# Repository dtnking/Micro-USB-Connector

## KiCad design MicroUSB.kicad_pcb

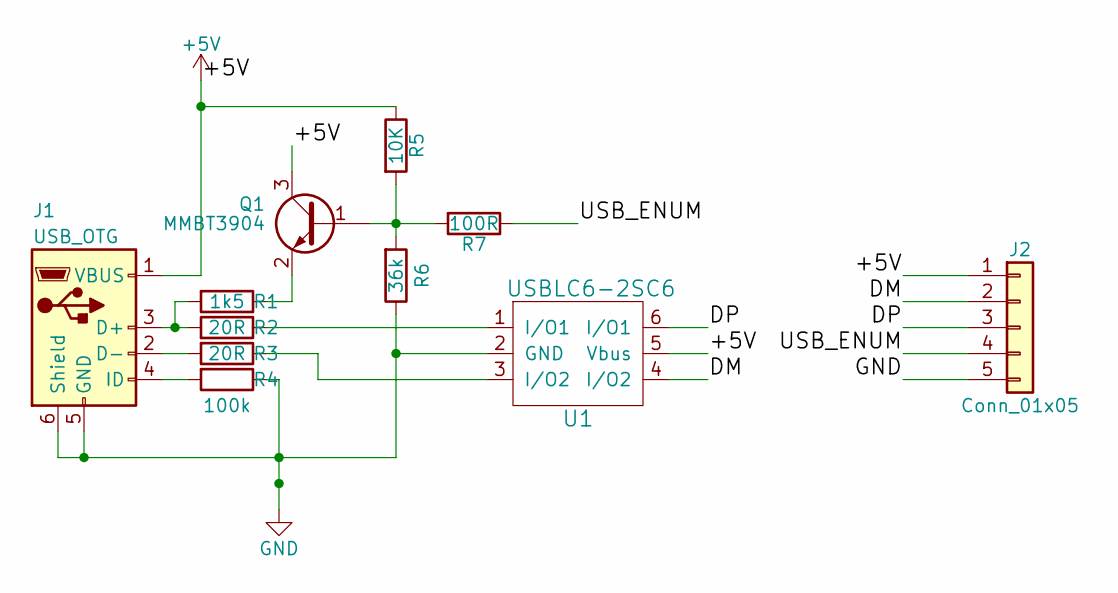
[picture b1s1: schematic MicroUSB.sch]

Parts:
J1: USB_OTG; USB_Micro-B_Molex-105017-0001
J2: Conn_01x05; Pin_Header_Straight_1x05_Pitch2.54mm
Q1: MMBT3904; SOT-23
R1: 1k5; R_0603
R2, R3: 20R; R_0603
R4: 100k; R_0603
R5: 10K; R_0603
R6: 36k; R_0603
R7: 100R; R_0603
U1: USBLC6-2SC6; SOT-23-6

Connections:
+5V: J1.1 (VBUS), J2.1, Q1.3 (C), R5.1, U1.5 (Vbus)
/DM: J2.2, U1.4 (I/O2)
/DP: J2.3, U1.6 (I/O1)
/USB_ENUM: J2.4, R7.1
GND: J1.5 (GND), J1.6 (Shield), J2.5, R4.1, R6.1, U1.2 (GND)
unnamed: J1.2 (D-), R3.2
unnamed: J1.3 (D+), R1.2, R2.2
unnamed: J1.4 (ID), R4.2
unnamed: Q1.1 (B), R5.2, R6.2, R7.2
unnamed: Q1.2 (E), R1.1
unnamed: R2.1, U1.1 (I/O1)
unnamed: R3.1, U1.3 (I/O2)

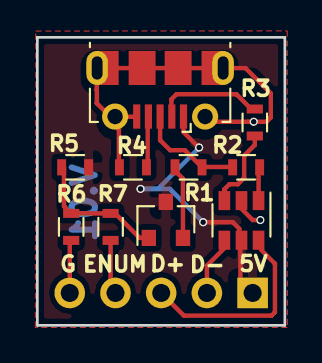
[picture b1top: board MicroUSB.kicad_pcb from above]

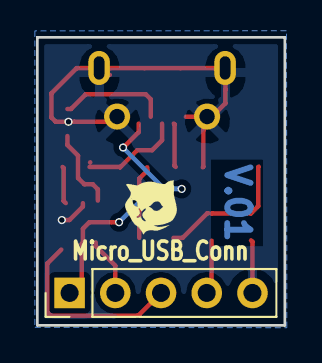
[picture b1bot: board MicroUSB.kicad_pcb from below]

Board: 2 copper layers, 13.8 x 16.0 mm, 12 parts (2 on the bottom side), 12 nets.

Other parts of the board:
Kitty: G***; Kitty

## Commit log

2017-10-12 Added micro usb connector Design
2017-10-13 Re-designed (using non-handsolder footprint)
2017-10-24 Moved the top edge cut further inwards
2017-11-07 Changed the size of text to 0.8x1.0 mm
2017-11-14 Added dimension and changed DM/DP label to D+/D-
2017-11-15 Added a txt V.01 indicated version 1 and added gerber file for panelizing
2017-11-27 Created a new microUSB footprint and replaced the old one
2017-12-10 Changed the clearance of coppoer pour to 0.3mm and changed the footprint of micro usb
2017-12-11 Moved the micro USB out 0.7mm from edge to edge
